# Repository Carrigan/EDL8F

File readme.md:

#Event Driven LPC800 Framework

## Purpose
The purpose of the Event Driven LPC800 Framework (EDL8F) is to provide a 
simple interrupt driven framework for the LPC800 microcontroller. The EDL8F
manages events and provides language for users to implement
non-blocking, energy efficient solutions. This framework aims to be as user
friendly as Arduino- using a similar setup() function. Instead of a synchronous
looping function which controls program flow, the user defines which events will
wake the processor, and what the processor should do before falling back asleep. 
Since the LPC800 uses a switch matrix for all of its peripherals, this library
will also provide a routing function which allows the user to configure where
peripherals are located from within code.

Please see the Usage section for framework syntax, and the Examples section for 
the intended use of this library.

## Usage
- void setup(void)
  - This function is called during intialization one time, and should contain the user's initialization code.
- void onPERIPHERALNAME(arg0, arg1, ..., argN)
  - This function is called when an interrupt is processed by the Event Manager. 
  - For example, if a Wakeup Timer interrupt occured, the user's onWKT(void) function will be called.
  - Events such as UART and I2C will return their data using arguments as defined by each peripheral.
- void process(void)
  - This function resembles the loop() function in Arduino, but instead of being called in a repetitive fashion, it is called once all of the events have been handled and the processor is returning to sleep mode.
  - This function is meant to check flags set during interrupts and perform actions accordingly.

## Status

This framework is planned to be used on the LPC800-MAX board from NXP. This board will
provide a cheap and easy way for hobbyists to break into the ARM market. The `brd` folder
contains the gerbers for an LPC812M101FDH20 board which breaks out pins MBed style, 
contains a standard SWD programming header, pulls the boot and reset lines high, and 
provides a decoupling cap. This board was ordered on 4/28/13, and has not yet been tested.

## Modules

- EventManager Module
  - Queue module which accepts event data during interrupts to process later, in order.
- SystemManager Module
  - Module which builds upon the EDL8F peripheral layer and provides initialization routines and higher level peripheral access.

## Examples

Since this project is still in its infancy, the examples section is meant as the _intent_ of this framework. All examples are subject to change. For any currently working examples, check the examples directory.

### Example 1: Blinky

    void setup()
    {	
    	// Set up pin 11 as a push/pull output.
    	gpio_pinMode(P11, OUTPUT_PUSHPULL);
    	
    	// Set up the Wake-Up Timer to interrupt every 500ms.
    	setupWktTimer(500);
    }
    
    void onWkt()
    {
    	// Toggle the pin
    	gpio_togglePin(P11);
    }

### Example 2: UART Loopback
	// UART code has not been written -- this is the intent of the library.
	
    void setup()
    {
        route(UART_TX0, P1);
        route(UART_RX0, P2);
        setupUart(UART0, 9600, UART_NONE);
        
        wakeupOn(UART0);
    }

    onUART0()
    {
        uint8_t incomingData = uartRead(UART0);
        uartWrite(UART0, incomingData);
    }

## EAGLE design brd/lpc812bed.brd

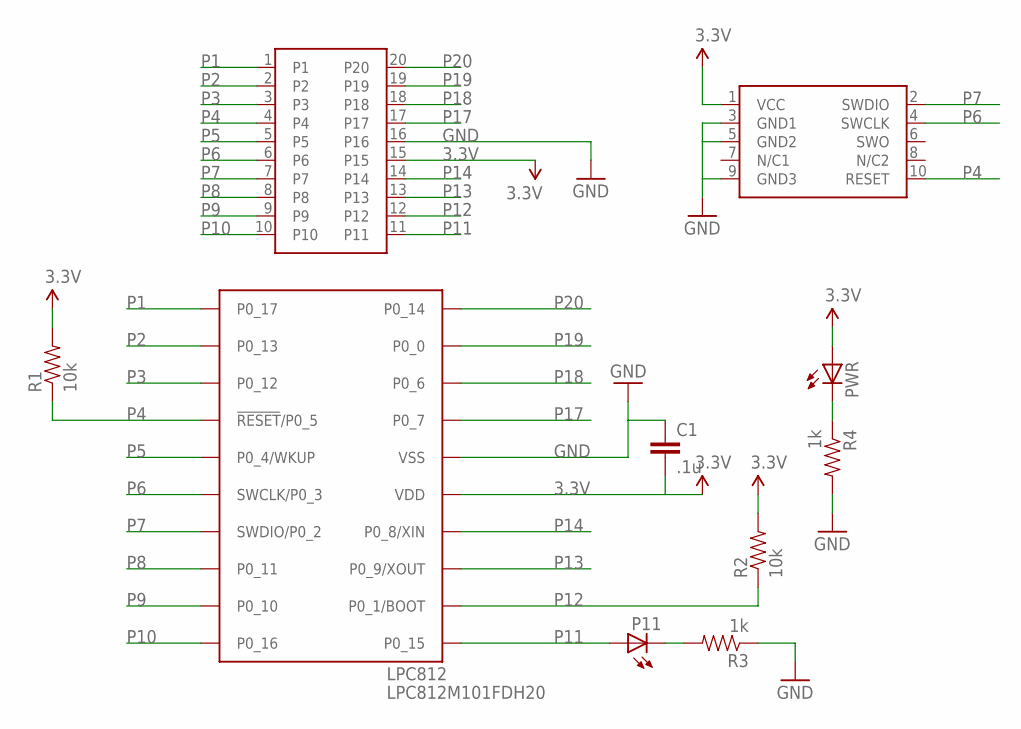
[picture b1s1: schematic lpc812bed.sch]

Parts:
C1: .1u; 0805
LPC812: LPC812M101FDH20; TSSOP20
P11: LED1206; LED-1206
PWR: LED1206; LED-1206
R1, R2: 10k; 1206
R3, R4: 1k; 1206
SWD1: CORTEX_SWD; M50-3600542
U$2: LPCBOARD; LPCBOARD_SPACERS

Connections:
3.3V: C1.2, LPC812.15 (VDD), PWR.A, R1.2, R2.2, SWD1.1 (VCC), U$2.15
GND: C1.1, LPC812.16 (VSS), R3.1, R4.2, SWD1.3 (GND1), SWD1.5 (GND2), SWD1.9 (GND3), U$2.16
unnamed: P11.C, R3.2
unnamed: PWR.C, R4.1
P1: LPC812.1 (P0_17), U$2.1
P2: LPC812.2 (P0_13), U$2.2
P3: LPC812.3 (P0_12), U$2.3
P4: LPC812.4 (!RESET!/P0_5), R1.1, SWD1.10 (RESET), U$2.4
P5: LPC812.5 (P0_4/WKUP), U$2.5
P6: LPC812.6 (SWCLK/P0_3), SWD1.4 (SWCLK), U$2.6
P7: LPC812.7 (SWDIO/P0_2), SWD1.2 (SWDIO), U$2.7
P8: LPC812.8 (P0_11), U$2.8
P9: LPC812.9 (P0_10), U$2.9
P10: LPC812.10 (P0_16), U$2.10
P11: LPC812.11 (P0_15), P11.A, U$2.11
P12: LPC812.12 (P0_1/BOOT), R2.1, U$2.12
P13: LPC812.13 (P0_9/XOUT), U$2.13
P14: LPC812.14 (P0_8/XIN), U$2.14
P17: LPC812.17 (P0_7), U$2.17
P18: LPC812.18 (P0_6), U$2.18
P19: LPC812.19 (P0_0), U$2.19
P20: LPC812.20 (P0_14), U$2.20

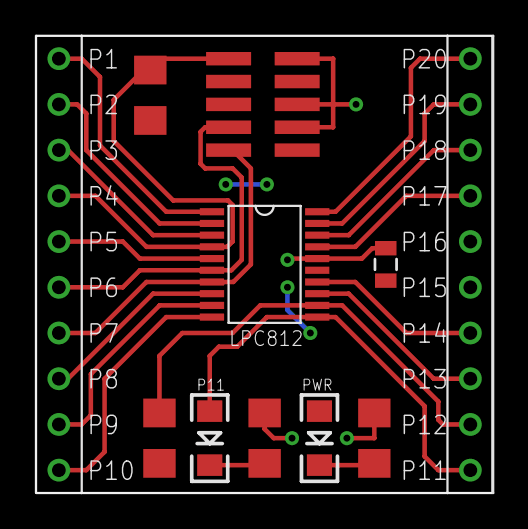
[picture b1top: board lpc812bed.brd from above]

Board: 2 copper layers, 25.3 x 25.4 mm, 10 parts (0 on the bottom side), 22 nets.

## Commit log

2013-04-24 Initial commit outlining intent and event queueing.
2013-04-26 Got rid of MSVC portion, serialized EventManager, added SystemManager, began adding peripherals.
2013-04-27 Added a simple LPC812 MBED style board with SWD interface, 2 LEDs, and decoupling caps.
2013-04-28 Fixed silks, ordered one board.
2013-04-29 Added license, first example, and better explanations of the project.

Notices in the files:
parts and their libraries:
SparkFun-Resistors: Licensing: CC v3.0 Share-Alike You are welcome to use this library for commercial purposes.
